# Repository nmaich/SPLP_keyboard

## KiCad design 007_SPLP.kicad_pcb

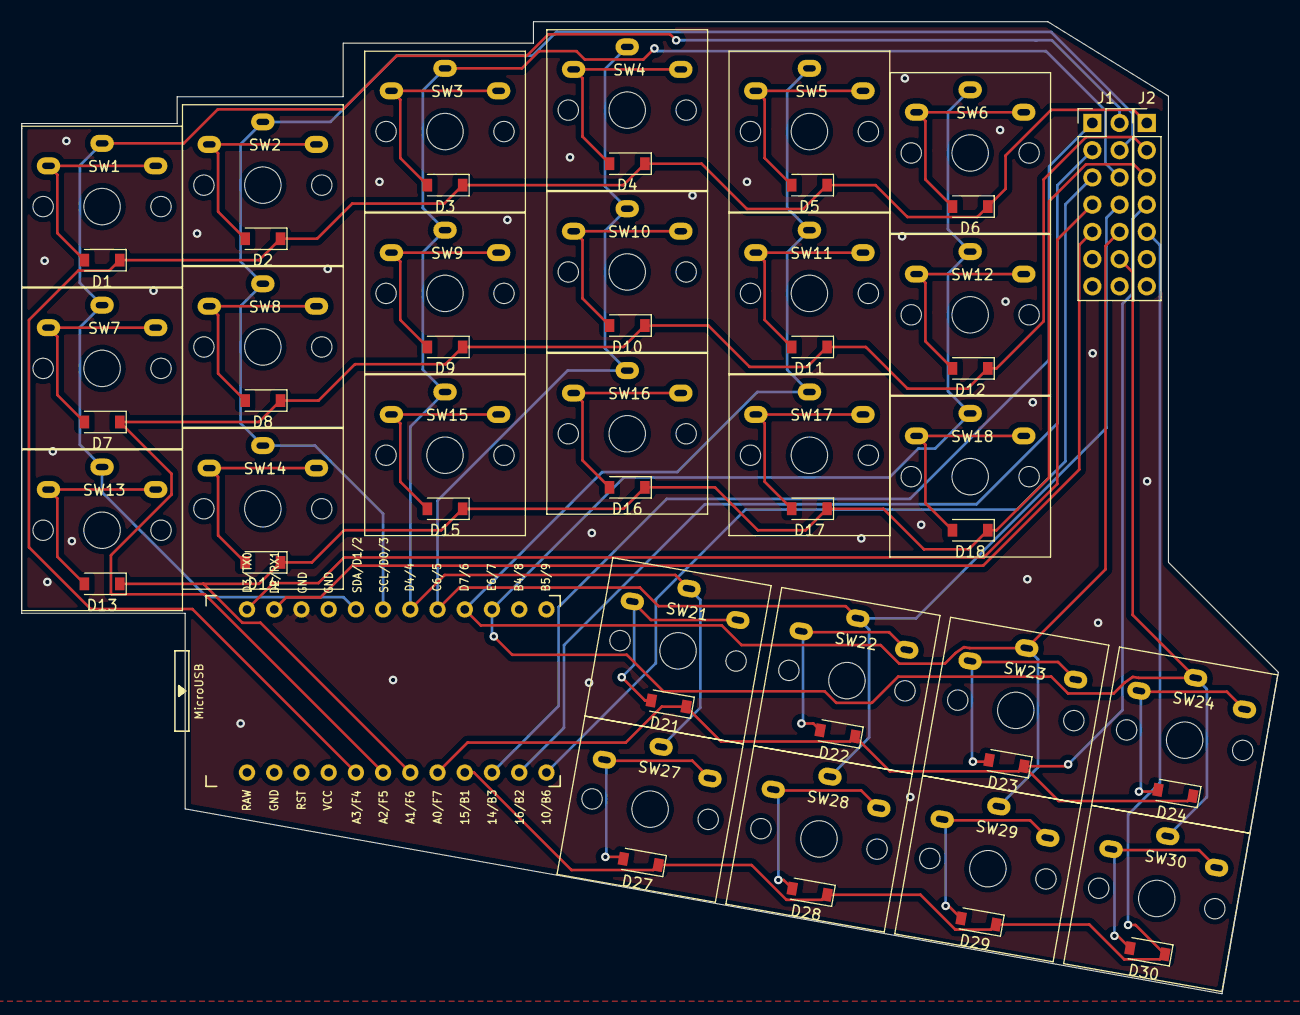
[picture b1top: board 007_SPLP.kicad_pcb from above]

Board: 2 copper layers, 117.2 x 90.7 mm, 55 parts (0 on the bottom side), 42 nets.

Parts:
D1, D2, D3, D4, D5, D6, D7, D8, D9, D10, D11, D12, D13, D14, D15, D16, D17, D18, D21, D22, D23, D24, D27, D28, D29, D30: 1N4148; D_SOD-123
J1: Conn_02x07_Odd_Even; PinHeader_2x07_P2.54mm_Vertical
J2: Conn_01x07; PinHeader_1x07_P2.54mm_Vertical
SW1, SW2, SW3, SW4, SW5, SW6, SW7, SW8, SW9, SW10, SW11, SW12, SW13, SW14, SW15, SW16, SW17, SW18, SW21, SW22, SW23, SW24, SW27, SW28, SW29, SW30: SW_PUSH; choc_rev
U1: ProMicro_r; ProMicro_v3.5

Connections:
/a1: J1.1, U1.15
/a2: J1.3, U1.14
/a3: J1.5, U1.13
/a4: J1.7, U1.1
/a5: J1.9, U1.2
/col1: J1.2, SW1.1, SW7.1, SW13.1, U1.5
/col2: J1.4, SW2.1, SW8.1, SW14.1, U1.6
/col3: J1.6, SW3.1, SW9.1, SW15.1, SW21.1, SW27.1, U1.7
/col4: J1.8, SW4.1, SW10.1, SW16.1, SW22.1, SW28.1, U1.8
/col5: J1.10, SW5.1, SW11.1, SW17.1, SW23.1, SW29.1, U1.9
/col6: J1.12, SW6.1, SW12.1, SW18.1, SW24.1, SW30.1, U1.10
/row1: D1.1, D2.1, D3.1, D4.1, D5.1, D6.1, J2.1, U1.20
/row2: D7.1, D8.1, D9.1, D10.1, D11.1, D12.1, J2.2, U1.19
/row3: D13.1, D14.1, D15.1, D16.1, D17.1, D18.1, J2.3, U1.18
/row4: D21.1, D22.1, D23.1, D24.1, J2.4, U1.17
/row5: D27.1, D28.1, D29.1, D30.1, J2.5, U1.16
unnamed: D1.2, SW1.2
unnamed: D2.2, SW2.2
unnamed: D3.2, SW3.2
unnamed: D4.2, SW4.2
unnamed: D5.2, SW5.2
unnamed: D6.2, SW6.2
unnamed: D7.2, SW7.2
unnamed: D8.2, SW8.2
unnamed: D9.2, SW9.2
unnamed: D10.2, SW10.2
unnamed: D11.2, SW11.2
unnamed: D12.2, SW12.2
unnamed: D13.2, SW13.2
unnamed: D14.2, SW14.2
unnamed: D15.2, SW15.2
unnamed: D16.2, SW16.2
unnamed: D17.2, SW17.2
unnamed: D18.2, SW18.2
unnamed: D21.2, SW21.2
unnamed: D22.2, SW22.2
unnamed: D23.2, SW23.2
unnamed: D24.2, SW24.2
unnamed: D27.2, SW27.2
unnamed: D28.2, SW28.2
unnamed: D29.2, SW29.2
unnamed: D30.2, SW30.2
